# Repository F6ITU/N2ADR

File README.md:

# N2ADR
N2ADR HPF &amp;  lpf for the Hermes Lite V2 project (fork heavily modified) 

This fork of the original N2ADR filter project (https://github.com/softerhardware/Hermes-Lite2/tree/master/hardware/companions/n2adr )
is designed on less expansive 2 sides only PCB. This filter can be directly plugged on a Hermes Lite V2 board or installed as a "piggy back" extension
fixed over the HL2 main board. This way, all input/output of the transmission system are located on the main frontplate of the transceiver. 

  - TR/PTT I/O is now using the same stereo jack used on the HL2 board
  - RX only SMA plug has been added
  - "Low power TX" and "RX only" RF path are routed thru coaxial jumpers to avoid impedance mismatch 
  - A heavy stitching of the board compensates the lack of insulation between RF traces and command bus

A specific pcb frontpanel is under development to accomodate this new configuration. 

Caveat emptor : 

This fork is a prototype. If you don't like risks, please built the original design

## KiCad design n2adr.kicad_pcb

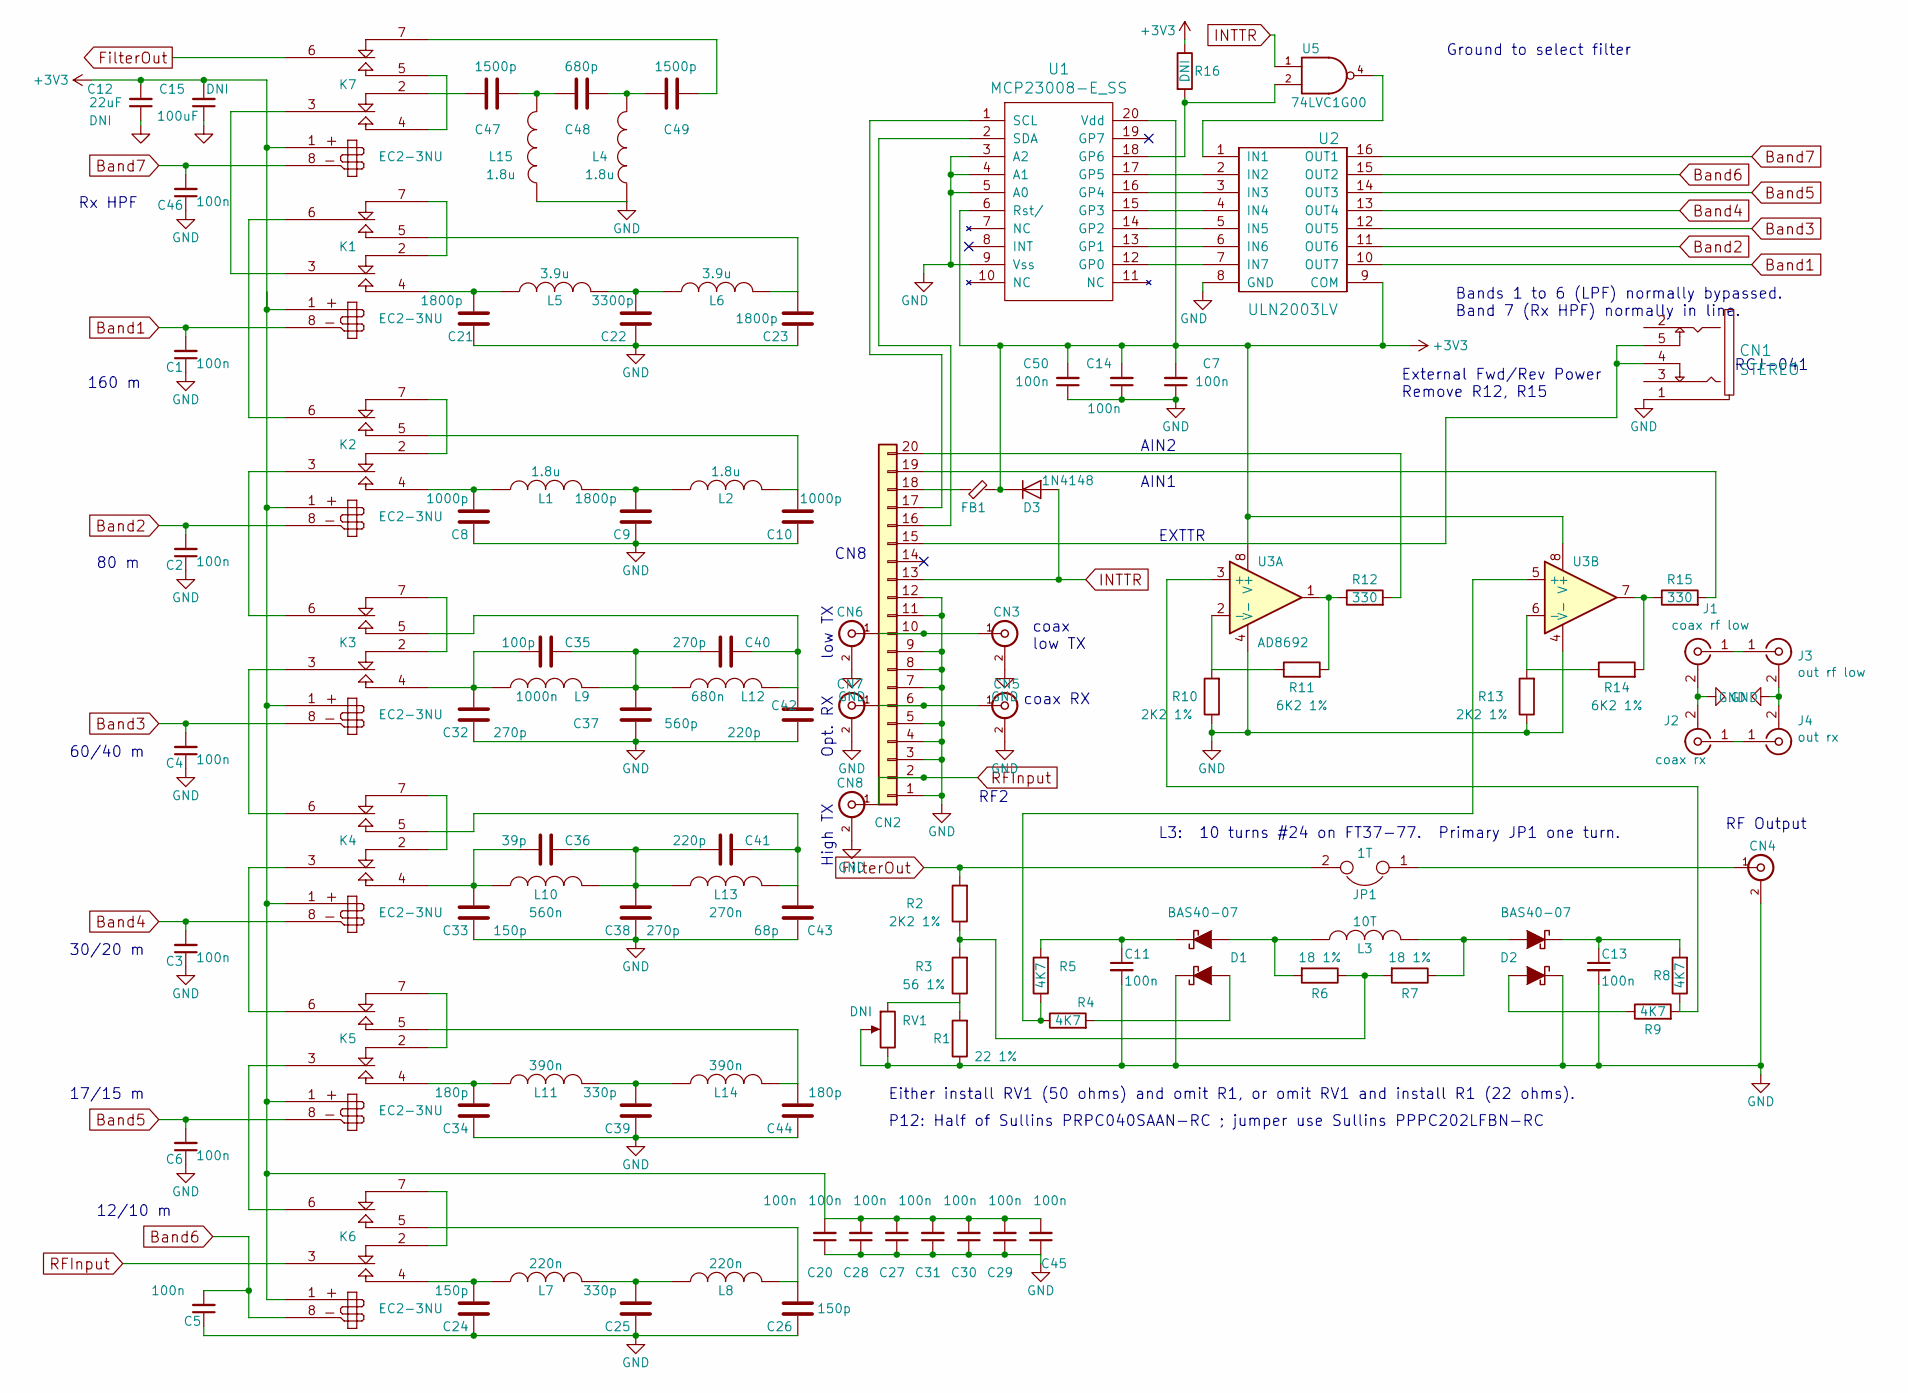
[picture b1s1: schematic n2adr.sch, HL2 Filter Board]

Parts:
C1, C2, C3, C4, C5, C6, C7, C11, C13, C14, C20, C27, C28, C29, C30, C31, C45, C46, C50: 100n; SMD_0805
C8, C10: 1000p; SMD_1206
C9, C21, C23: 1800p; SMD_1206
C12: 22uF; SMD_0805
C15: 100uF; SMD-1206
C22: 3300p; SMD_1206
C24, C26, C33: 150p; SMD_1206
C25, C39: 330p; SMD_1206
C32, C38, C40: 270p; SMD_1206
C34, C44: 180p; SMD_1206
C35: 100p; SMD_1206
C36: 39p; SMD_1206
C37: 560p; SMD_1206
C41, C42: 220p; SMD_1206
C43: 68p; SMD_1206
C47, C49: 1500p; SMD_0805
C48: 680p; SMD_0805
CN1: STEREO
CN2: Conn_01x20; Pin_Header_Straight_1x20_Pitch2.54mm
CN3: SMA; coax_2mm
CN4, CN6, CN7, CN8: SMA; SMA_EDGE_NRW
CN5: SMA; coax_1mm
D1, D2: BAS40-07; SOT-143
D3: 1N4148; D_SOD-123
FB1: FB; SMD_0805
J1: coax rf low; coax_2mm
J2: coax rx; coax_2mm
J3: out rf low; SMA_EDGE_NRW
J4: out rx; SMA_EDGE_NRW
JP1: 1T; WireConnection_1.20mmDrill
K1, K2, K3, K4, K5, K6, K7: EC2-3NU; RelayDPDT01
L1, L2: 1.8u; SMD_1812
L3: 10T; ToroidT37
L4, L15: 1.8u; SMD_0805
L5, L6: 3.9u; SMD_1812
L7, L8: 220n; SMD_1210
L9: 1000n; SMD_1812
L10: 560n; SMD_1210
L11, L14: 390n; SMD_1210
L12: 680n; SMD_1210
L13: 270n; SMD_1210
R1: 22 1%; SMD_0805
R2, R10, R13: 2K2 1%; SMD_0805
R3: 56 1%; SMD_0805
R4, R5, R8, R9: 4K7; SMD_0805
R6, R7: 18 1%; SMD_0805
R11, R14: 6K2 1%; SMD_0805
R12, R15: 330; SMD_0805
R16: DNI; SMD_0805
RV1: DNI; Trimpot_Bourns_3314G
U1: MCP23008-E_SS; SSOP-20_5.3x7.2mm_P0.65mm
U2: ULN2003LV; TSSOP-16_4.4x5mm_Pitch0.65mm
U3: AD8692; MSOP-8_3x3mm_Pitch0.65mm
U5: 74LVC1G00; SOT-23-5_HandSoldering

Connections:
+3V3: C7.2, C12.2, C14.2, C15.2, C20.2, C27.2, C28.2, C29.2, C30.2, C31.2, C45.2, C50.2, D3.1 (K), FB1.1, K1.1, K2.1, K3.1, K4.1, K5.1, K6.1, K7.1, R16.1, U1.6 (Rst/), U1.20 (Vdd), U2.9 (COM), U3.8 (V+), U5.5 (+3V3)
Band1: C1.2, K1.8, U2.10 (OUT7)
Band2: C2.2, K2.8, U2.11 (OUT6)
Band3: C4.2, K3.8, U2.12 (OUT5)
Band4: C3.2, K4.8, U2.13 (OUT4)
Band5: C6.2, K5.8, U2.14 (OUT3)
Band6: C5.2, K6.8, U2.15 (OUT2)
Band7: C46.2, K7.8, U2.16 (OUT1)
FilterOut: JP1.2, K7.6, R2.2
GND: C1.1, C2.1, C3.1, C4.1, C5.1, C6.1, C7.1, C8.1, C9.1, C10.1, C11.2, C12.1, C13.2, C14.1, C15.1, C20.1, C21.2, C22.2, C23.2, C24.1, C25.1, C26.1, C27.1, C28.1, C29.1, C30.1, C31.1, C32.1, C33.1, C34.1, C37.1, C38.1, C39.1, C42.1, C43.1, C44.1, C45.1, C46.1, C50.1, CN1.1, CN2.1, CN2.3, CN2.4, CN2.5, CN2.7, CN2.8, CN2.9, CN2.11, CN2.12, CN3.2 (Ext), CN4.2 (Ext), CN5.2 (Ext), CN6.2 (Ext), CN7.2 (Ext), CN8.2 (Ext), D1.1 (K), D2.2 (K), J1.2 (Ext), J2.2 (Ext), J3.2 (Ext), J4.2 (Ext), L4.1, L15.1, R1.1, R10.1, R13.1, RV1.2, RV1.3, U1.3 (A2), U1.4 (A1), U1.5 (A0), U1.9 (Vss), U2.8 (GND), U3.4 (V-), U5.3 (GND)
INTTR: CN2.13, D3.2 (A), U5.1
unnamed: C8.2, K2.4, L1.1
unnamed: C9.2, L1.2, L2.1
unnamed: C10.2, K2.5, L2.2
unnamed: C11.1, D1.2 (K), R5.2
unnamed: C13.1, D2.1 (K), R8.2
unnamed: C21.1, K1.4, L5.1
unnamed: C22.1, L5.2, L6.1
unnamed: C23.1, K1.5, L6.2
unnamed: C24.2, K6.4, L7.1
unnamed: C25.2, L7.2, L8.1
unnamed: C26.2, K6.5, L8.2
unnamed: C32.2, C35.2, K3.4, L9.1
unnamed: C33.2, C36.2, K4.4, L10.1
unnamed: C34.2, K5.4, L11.1
unnamed: C35.1, C37.2, C40.2, L9.2, L12.1
unnamed: C36.1, C38.2, C41.2, L10.2, L13.1
unnamed: C39.2, L11.2, L14.1
unnamed: C40.1, C42.2, K3.5, L12.2
unnamed: C41.1, C43.2, K4.5, L13.2
unnamed: C44.2, K5.5, L14.2
unnamed: C47.1, C48.2, L15.2
unnamed: C47.2, K7.2
unnamed: C48.1, C49.2, L4.2
unnamed: C49.1, K7.7
unnamed: CN1.4, CN1.5, CN2.15
unnamed: CN2.6, CN5.1 (In), CN7.1 (In)
unnamed: CN2.10, CN3.1 (In), CN6.1 (In)
unnamed: CN2.16, U1.2 (SDA)
unnamed: CN2.17, U1.1 (SCL)
unnamed: CN2.18, FB1.2
unnamed: CN2.19, R15.2
unnamed: CN2.20, R12.2
unnamed: CN4.1 (In), JP1.1
unnamed: D1.3 (A), L3.1, R6.2
unnamed: D1.4 (A), R4.2
unnamed: D2.3 (A), R9.1
unnamed: D2.4 (A), L3.2, R7.1
unnamed: J1.1 (In), J3.1 (In)
unnamed: J2.1 (In), J4.1 (In)
unnamed: K1.2, K1.7
unnamed: K1.3, K7.3
unnamed: K1.6, K2.6
unnamed: K2.2, K2.7
unnamed: K2.3, K3.6
unnamed: K3.2, K3.7
unnamed: K3.3, K4.6
unnamed: K4.2, K4.7
unnamed: K4.3, K5.6
unnamed: K5.2, K5.7
unnamed: K5.3, K6.6
unnamed: K6.2, K6.7
unnamed: K7.4, K7.5
unnamed: R1.2, R3.1, RV1.1
unnamed: R2.1, R3.2, R6.1, R7.2
unnamed: R4.1, R5.1, U3.5 (+)
unnamed: R8.1, R9.2, U3.3 (+)
unnamed: R10.2, R11.1, U3.2 (-)
unnamed: R11.2, R12.1, U3.1
unnamed: R13.2, R14.1, U3.6 (-)
unnamed: R14.2, R15.1, U3.7
unnamed: R16.2, U1.18 (GP6), U5.2
unnamed: U1.12 (GP0), U2.7 (IN7)
unnamed: U1.13 (GP1), U2.6 (IN6)
unnamed: U1.14 (GP2), U2.5 (IN5)
unnamed: U1.15 (GP3), U2.4 (IN4)
unnamed: U1.16 (GP4), U2.3 (IN3)
unnamed: U1.17 (GP5), U2.2 (IN2)
unnamed: U2.1 (IN1), U5.4
RFInput: CN2.2, CN8.1 (In), K6.3

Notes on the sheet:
Ground to select filter
RF Output
L3: 10 turns #24 on FT37-77. Primary JP1 one turn.
80 m
60/40 m
30/20 m
17/15 m
12/10 m
160 m
RF2
EXTTR
AIN2
AIN1
CN8
Opt. RX
External Fwd/Rev Power Remove R12, R15
RCJ-041
P12: Half of Sullins PRPC040SAAN-RC ; jumper use Sullins PPPC202LFBN-RC
Either install RV1 (50 ohms) and omit R1, or omit RV1 and install R1 (22 ohms).
Rx HPF
Bands 1 to 6 (LPF) normally bypassed. Band 7 (Rx HPF) normally in line.
coax low TX
coax RX
low TX
High TX

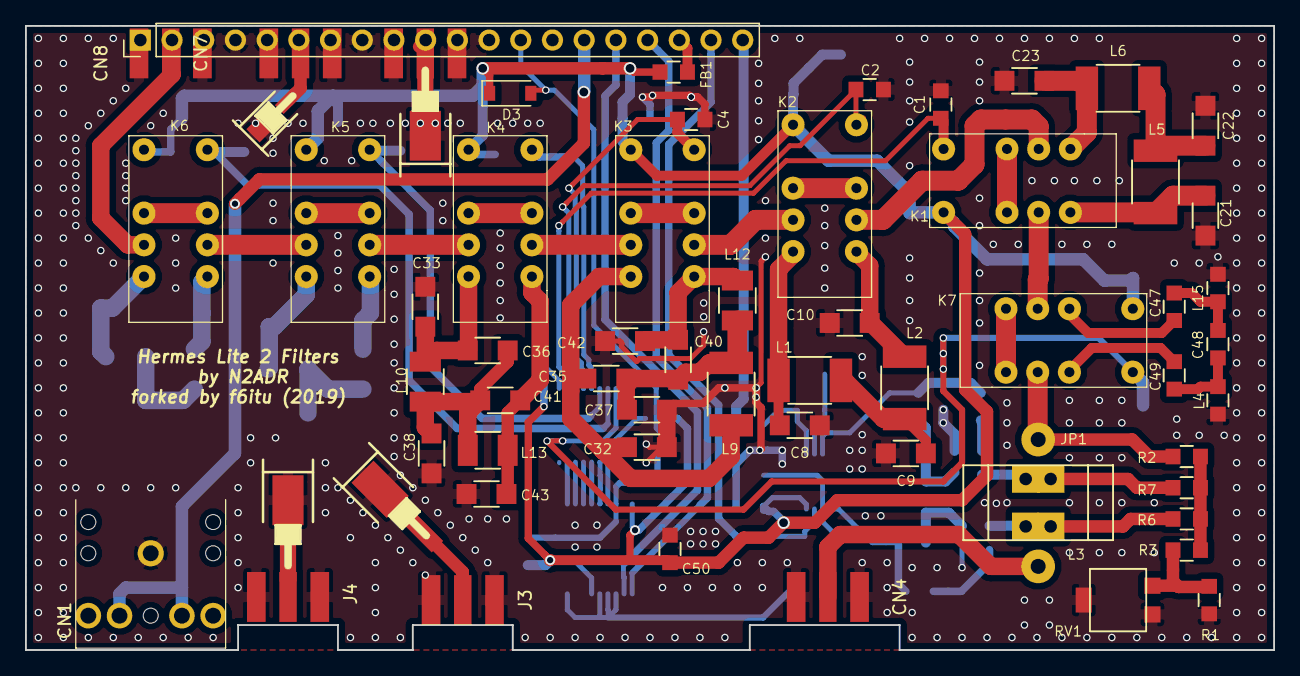
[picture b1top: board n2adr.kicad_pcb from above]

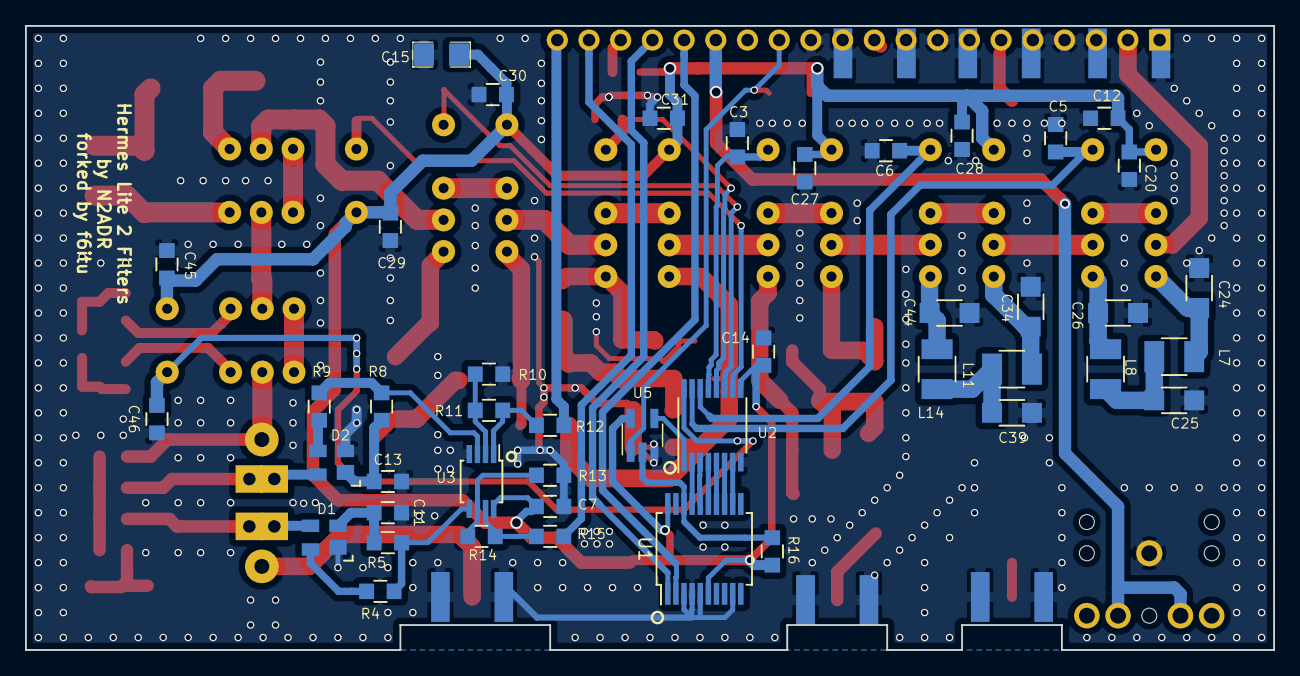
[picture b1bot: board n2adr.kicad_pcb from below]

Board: 4 copper layers, 100.0 x 50.0 mm, 106 parts (44 on the bottom side), 80 nets.

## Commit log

2019-03-01 first design, initial commit
2019-03-15 upgrade to Kicad 5.x, 2 layers less
2019-06-07 minor pcb changes still under dev
